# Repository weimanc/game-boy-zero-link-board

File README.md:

# Game-Boy-Zero-Link-Board

This project is forked from agtbaskara. This is the first time I'm using KiCad and Github. The experience is very pleasant to build on top of other people's work. Even this README.md is forked and extended ;). Check out the [References](#References).

Like agtbaskara, this is another Open-Source USB to Gameboy Link Cable Adapter based around the smaller and cheaper RP2040-Zero. Designed with components that are easy to source and solder.

Game-Boy-Zero-Link-Board offers multiple options to connect your GB link cable.
- J1 GBA/GBC PCB Edge connector
- J2 DMG PCB Edge connector
- J3 DMG/GBA/GBC/IDC combined footprint

Game-Boy-Zero-Link-Board uses GBVCC (PIN1 of the GB link cable) to power the HV side of the Logic Level Converter. This allows the board to autmatically resolve the correct voltage on the GB side.

Based on stacksmashing Gameboy Link adapter: https://www.youtube.com/watch?v=KtHu693wE9o

# Schematic

# Required Components

| Reference | Part Number | Description |
|-|-|-|
| U1 | [RP2040-Zero](https://www.waveshare.com/wiki/RP2040-Zero) | Waveshare RP2040-Zero |
| U1* | [RP2040-Zero](https://www.aliexpress.com/item/1005005994987953.html) | AliExpress RP2040-Zero |
| U2 | [BOB-12009](https://www.sparkfun.com/products/12009) | Sparkfun Bi-Directional Logic Level Converter, clones are compatible |
| U2* | [BOB-12009](https://www.aliexpress.com/item/1005006068381598.html) |  AliExpress Bi-Directional Logic Level Converter|
| J1/J2 | [DMG-GBC-cable](https://www.aliexpress.com/item/1005004110251579.html) | AliExpress link cable suitable for DMG and GBC|
| J3 | [GBA_link](https://www.aliexpress.com/item/1005006181192248.html) | AliExpress GBA link port |

**Attached links are for reference only, you can use any equivalent parts.**

# How to Order Board

To order a board, use the `gerbers*.zip` from the release page or generate one yourself. You can order from your favourite PCB manufacturer ([JLCPCB](https://jlcpcb.com/), [PCBWay](https://www.pcbway.com/), etc.).

**Use 1.2mm PCB thickness.**

You can choose any colour for the Solder Mask and Silkscreen. For the Surface Finish, ENIG is recommended.

# How to Assemble Board

1. Solder pin header to RP2040-Zero and Level Shifter module. Use a breadboard for easier soldering
2. Solder RP2040-Zero and Level Shifter module to the board
3. Cut the excessive pin using a nipper tool
4. Flash firmware to your RP2040-Zero (see [Compatibility](#Compatibility))

# How to Use Board

Connect the board to your PC, and connect the board to your Gameboy using a Link Cable.

# Compatibility

This board is compatible with the following firmware:
- https://github.com/stacksmashing/gb-link-firmware
- https://github.com/stacksmashing/gb-link-printer
- https://github.com/Lorenzooone/PokemonGB_Online_Trades
- https://github.com/dj505/GBPrinterEmu
- https://github.com/Squaresweets/GBPrinter-discord-bot
- https://github.com/KuestenKeks/pc-to-gb-printer
- https://github.com/PaulMDemers/poke-link

With some modification, it should be compatible with other firmware as well, such as:
- https://github.com/untoxa/pico-gb-printer

# References
- Game-Boy-Pico-Link-Board: https://github.com/agtbaskara/game-boy-pico-link-board
- Waveshare RP2040-Zero Footprint: https://files.waveshare.com/upload/f/f7/RP2040_Zero_stp.zip
- Logic Level Converter (BOB-12009) Footprint: https://www.snapeda.com/parts/BOB-12009/SparkFun%20Electronics/view-part/
- Gameboy Link Connector Footprint: https://github.com/Palmr/gb-link-cable
- Gameboy Link Port Footprint: https://github.com/Gekkio/gb-hardware
- 1.2mm PCB Thickness, based on: https://hackaday.io/project/12932-game-link-online/log/43999-received-the-breakout-boards
- Print your own DMG link cable plug: https://www.thingiverse.com/thing:4685189

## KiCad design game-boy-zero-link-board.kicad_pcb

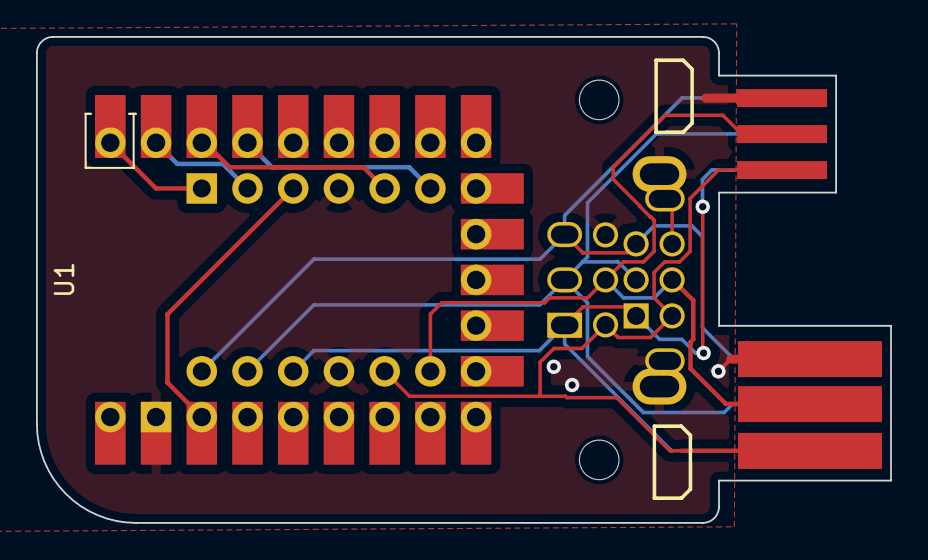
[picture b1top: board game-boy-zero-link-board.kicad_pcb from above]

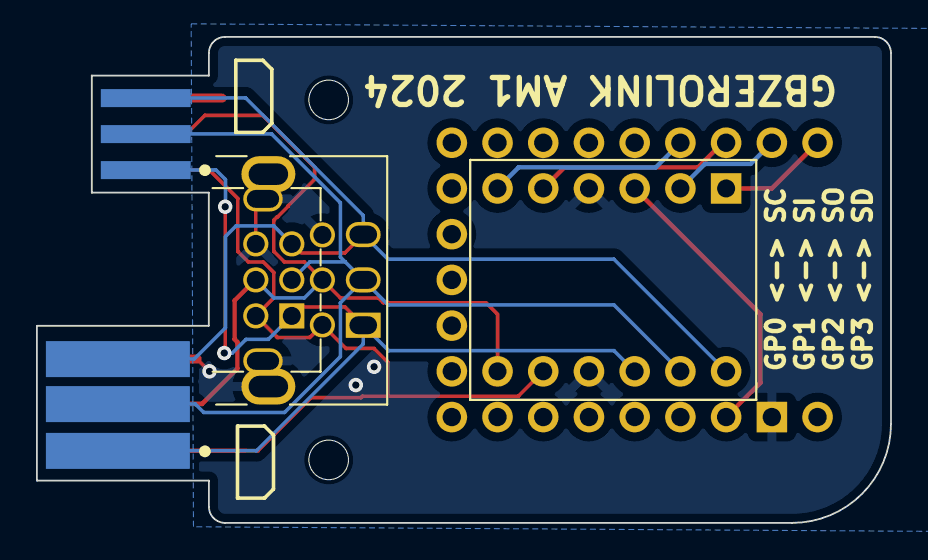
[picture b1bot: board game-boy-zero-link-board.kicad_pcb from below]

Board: 2 copper layers, 47.5 x 27.0 mm, 5 parts (2 on the bottom side), 11 nets.

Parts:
J1: GBA_Link; gb-link-socket
J2: DMG_Link; dmg-link-socket
J3: GB_IDC_port; GameBoy_LinkPort_DMG_MGB_IDC_Horizontal
U1: RP2040-Zero; RP2040-Zero_SMD_TH
Ue: BOB-12009

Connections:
+3.3V: U1.21 (3V3), Ue.3 (LV)
/GBVCC: J1.1, J2.1, J3.1, Ue.9 (HV)
/PSC: U1.1 (GPIO0), Ue.1 (LV1)
/PSD: U1.4 (GPIO3), Ue.6 (LV4)
/PSI: U1.2 (GPIO1), Ue.2 (LV2)
/PSO: U1.3 (GPIO2), Ue.5 (LV3)
/SC: J1.5, J2.5, J3.5, Ue.7 (HV1)
/SD: J1.4, J2.4, J3.4, Ue.12 (EL)
/SI: J1.3, J2.3, J3.3, Ue.8 (HV2)
/SO: J1.2, J2.2, J3.2, Ue.11 (HV3)
GND: J1.6, J2.6, J3.6, J3.SH, U1.22 (GND), Ue.4 (GND_1), Ue.10 (GND_2)

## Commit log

2024-01-20 Rename and prep project -Rename files to reflect new project name: game-boy-pico-link-board -remove gerbers/paste files -remove lck file -add *.lck in git ignore
2024-01-20 commit local changes (untested)
2024-01-20 Made some correction in the README.md add schematic.pdf, board-back-3d-bare.png adjust PCB thickness to 1.2mm and export game-boy-zero-link-board.wrl add missing library files
2026-04-09 Added poke-link to compatible firmwares
